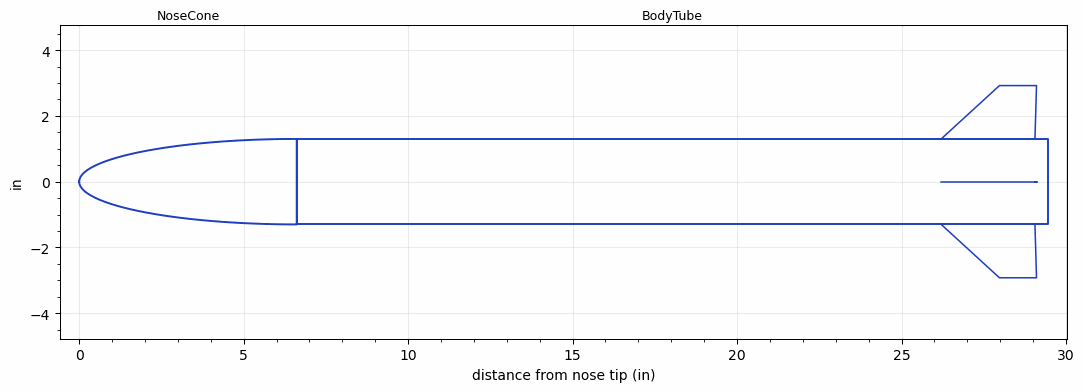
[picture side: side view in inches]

<RASAeroDocument>
 <FileVersion>2</FileVersion>
 <RocketDesign>
  <NoseCone>
   <Length>6.6142</Length>
   <Diameter>2.5984</Diameter>
   <Shape>Elliptical</Shape>
   <Location>0</Location>
  </NoseCone>
  <BodyTube>
   <Length>22.8346</Length>
   <Diameter>2.5984</Diameter>
   <Location>6.6142</Location>
   <Fin>
    <Count>4</Count>
    <Chord>2.8504</Chord>
    <Span>1.622</Span>
    <SweepDistance>1.7716</SweepDistance>
    <TipChord>1.126</TipChord>
    <Thickness>0.1181</Thickness>
    <Location>3.2441</Location>
    <AirfoilSection>Square</AirfoilSection>
   </Fin>
  </BodyTube>
  <Surface>Rough Camouflage Paint</Surface>
  <CD>0</CD>
  <ModifiedBarrowman>False</ModifiedBarrowman>
  <Turbulence>False</Turbulence>
  <UseBooster1>False</UseBooster1>
  <UseBooster2>False</UseBooster2>
  <Comments>V1</Comments>
 </RocketDesign>
 <LaunchSite>
  <Altitude>0</Altitude>
  <Pressure>29.9214</Pressure>
  <RodAngle>0</RodAngle>
  <RodLength>39.37</RodLength>
  <Temperature>59</Temperature>
  <WindSpeed>4.4739</WindSpeed>
 </LaunchSite>
 <Recovery>
  <Altitude1>0</Altitude1>
  <Altitude2>0</Altitude2>
  <DeviceType1>None</DeviceType1>
  <DeviceType2>None</DeviceType2>
  <Event1>False</Event1>
  <Event2>False</Event2>
  <Size1>0</Size1>
  <Size2>0</Size2>
  <EventType1>None</EventType1>
  <EventType2>None</EventType2>
  <CD1>0</CD1>
  <CD2>0</CD2>
 </Recovery>
 <SimulationList>
  <Simulation>
   <SustainerLaunchWt>1.4462</SustainerLaunchWt>
   <SustainerCG>13.7795</SustainerCG>
   <SustainerIgnitionDelay>0</SustainerIgnitionDelay>
   <Booster1SeparationDelay>0</Booster1SeparationDelay>
   <Booster1IgnitionDelay>0</Booster1IgnitionDelay>
   <IncludeBooster1>False</IncludeBooster1>
   <Booster2Delay>0</Booster2Delay>
   <IncludeBooster2>False</IncludeBooster2>
  </Simulation>
  <Simulation>
   <SustainerLaunchWt>1.4462</SustainerLaunchWt>
   <SustainerCG>13.7795</SustainerCG>
   <SustainerIgnitionDelay>0</SustainerIgnitionDelay>
   <Booster1SeparationDelay>0</Booster1SeparationDelay>
   <Booster1IgnitionDelay>0</Booster1IgnitionDelay>
   <IncludeBooster1>False</IncludeBooster1>
   <Booster2Delay>0</Booster2Delay>
   <IncludeBooster2>False</IncludeBooster2>
  </Simulation>
  <Simulation>
   <SustainerEngine>G74W  (AT)</SustainerEngine>
   <SustainerLaunchWt>1.638</SustainerLaunchWt>
   <SustainerCG>15.3768</SustainerCG>
   <SustainerIgnitionDelay>0</SustainerIgnitionDelay>
   <Booster1SeparationDelay>0</Booster1SeparationDelay>
   <Booster1IgnitionDelay>0</Booster1IgnitionDelay>
   <IncludeBooster1>False</IncludeBooster1>
   <Booster2Delay>0</Booster2Delay>
   <IncludeBooster2>False</IncludeBooster2>
  </Simulation>
 </SimulationList>
</RASAeroDocument>
